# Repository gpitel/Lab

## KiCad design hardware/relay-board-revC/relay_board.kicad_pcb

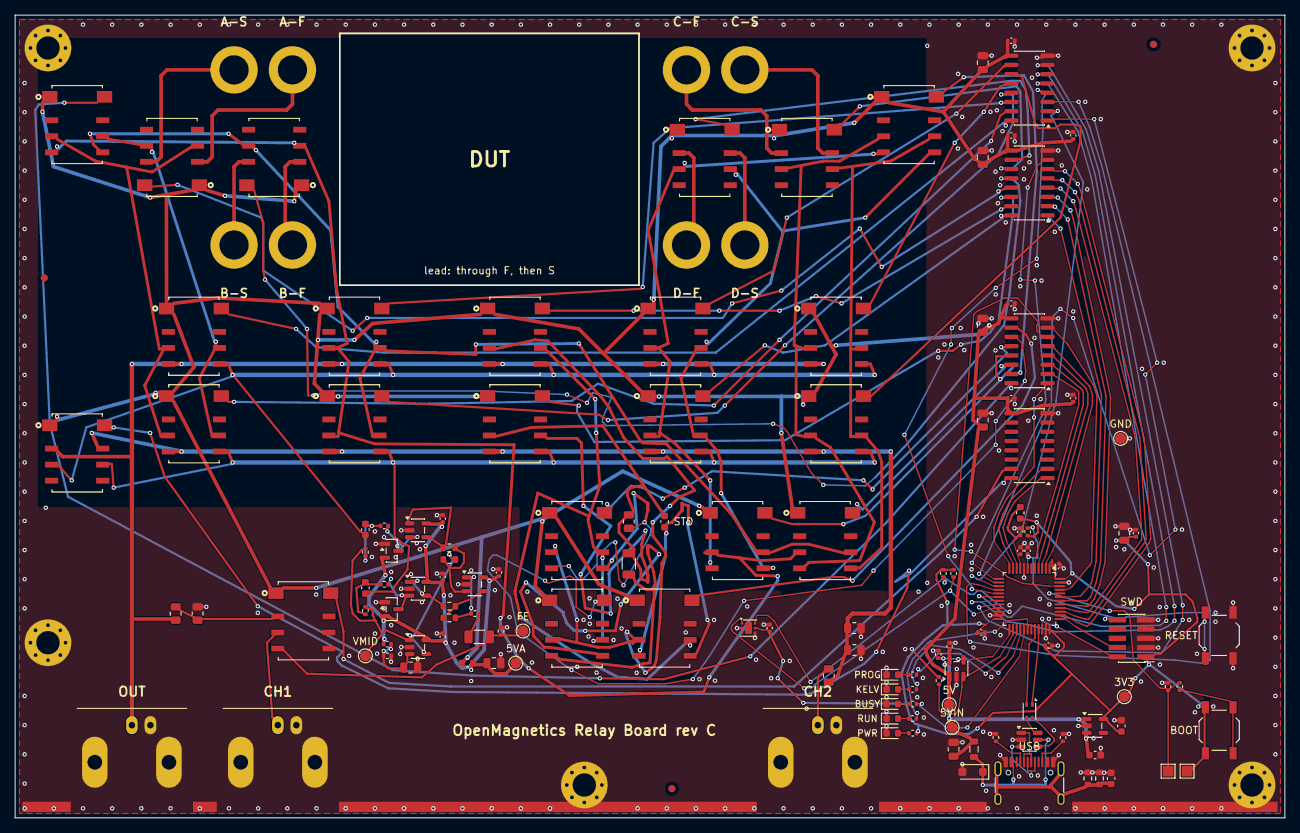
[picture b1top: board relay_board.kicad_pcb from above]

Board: 4 copper layers, 174.0 x 110.0 mm, 158 parts (0 on the bottom side), 126 nets.

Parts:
BOND1, BOND2, BOND3, BOND4, BOND5: GND bonding strip; GND_BondingStrip
C1, C2, C23, C29, C32, C33, C34, C35: C_0805_2012Metric
C3, C4, C20, C21, C30, C31: C_0603_1608Metric
C5, C6, C7, C8, C9, C10, C11, C12, C15, C16, C17, C18, C19, C25, C26, C27, C28, C36, C37: C_0402_1005Metric
C22: C_1206_3216Metric
D1, D5, D6, D7, D8: LED_0603_1608Metric
D2: SOT-23-6
D3, D4: SOT-23
D9: D_SOD-123F
FB1: L_0805_2012Metric
FB2, FB3: L_0603_1608Metric
FID1, FID2, FID3: Fiducial_1mm_Mask2mm
H1, H2, H3, H4, H5: MountingHole_3.2mm_M3_Pad_Via
J1: USB_C_Receptacle_HRO_TYPE-C-31-M-12
J6, J7, J9: BNC_Amphenol_B6252HB-NPP3G-50_Horizontal
J8: PinHeader_2x05_P1.27mm_Vertical_SMD
J10, J11, J12, J13, J14, J15, J16, J17: Grayhill 02-21; Grayhill_02-21_BananaPlug_4mm
K1, K2, K3, K4, K5, K6, K7, K8, K9, K10, K11, K12, K13, K14, K15, K16, K17, K18, K19, K20, K21, K22, K23: G6K-2F-RF-S; Relay_Omron_G6K-2F-RF-S
L1: L_CommonModeChoke_Coilank_ACM2012
NT1, NT2, NT4, NT5: NetTie-2_SMD_Pad0.5mm
R1, R2, R3, R4, R10, R17, R20, R21, R22, R23, R28, R29, R30, R31, R32, R33, R34, R35, R38, R39, R40, R41: R_0402_1005Metric
R5, R12, R13, R14, R15, R16: R_0805_2012Metric
R18: R_1206_3216Metric
R24, R25, R26, R27, R36, R37: R_0603_1608Metric
SW1, SW2: SW_SPST_TL3342
TP1, TP2: TestPoint_Pad_1.5x1.5mm
TP3, TP4, TP5, TP6, TP7, TP8, TP9: TestPoint_Pad_D1.5mm
U1: LQFP-48_7x7mm_P0.5mm
U2, U3, U4, U6: SOIC-16_3.9x9.9mm_P1.27mm
U5, U7, U8, U9, U10, U11: SOT-23-5
U12: WSON-6-1EP_2x2mm_P0.65mm_EP1x1.6mm

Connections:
/+3V3: C2.1, C4.1, C8.1, C9.1, C16.1, C17.1, C36.1, FB3.1, J8.1, R3.1, R32.1, R38.2, R39.2, R41.2, SW1.1, TP2.1, TP5.1, U1.1, U1.24, U1.36, U1.48, U5.5, U12.5
/+3V3A: C18.1, C19.1, FB3.2, U1.9
/+5V: C5.1, C6.1, C7.1, C10.1, C11.1, C12.1, C32.1, C33.1, C34.1, C35.1, FB2.1, K1.1, K2.1, K3.1, K4.1, K5.1, K6.1, K7.1, K8.1, K9.1, K10.1, K11.1, K12.1, K13.1, K14.1, K15.1, K16.1, K17.1, K18.1, K19.1, K20.1, K21.1, K22.1, K23.1, TP3.1, U2.9, U3.9, U4.9, U6.9, U11.1
/+5VA: C25.1, C26.1, C27.1, C28.1, C29.1, D3.2, D4.2, FB2.2, R30.1, TP6.1, U7.5, U8.5, U9.5, U10.5
/+5V_IN: C1.1, C3.1, C37.1, FB1.2, TP4.1, U5.1, U5.3, U11.5
/BOOT0: R4.1, R17.2, TP1.1, U1.44
/BOOT_SW: R17.1, SW1.2
/BUSY_A: D6.2, R33.2
/CAL_E: K9.3, K19.3, K20.3, K21.3
/CAL_ES: K9.6, K19.6, K20.6, K21.6
/CAL_F: C30.2, K10.3, NT2.1, R5.2, R18.2
/CAL_FS: K10.6, NT2.2
/CC1: J1.A5, R1.1
/CC2: J1.B5, R2.1
/CH1_BNC: J7.1, K23.3
/CH1_NODE: K23.2, R12.2, R13.1
/CH2_NODE: J9.1, R16.2
/COIL_EN: R40.1, U1.25, U11.4
/COIL_FLT: R41.1, U1.26, U11.3
/DUTS_A: J11.1, K11.7
/DUTS_B: J13.1, K12.7
/DUTS_C: J15.1, K13.7
/DUTS_D: J17.1, K14.7
/DUT_A: J10.1, K11.2
/DUT_B: J12.1, K12.2
/DUT_C: J14.1, K13.2
/DUT_D: J16.1, K14.2
/FE_AMP: R25.2, R28.1, U9.1
/FE_BN: R24.1, U8.1, U8.4
/FE_BP: R26.1, U7.1, U7.4
/FE_DM: R24.2, R25.1, U9.4
/FE_DP: R26.2, R27.1, U9.3
/FE_INN: C21.2, R22.1, R23.1
/FE_INP: C20.2, R20.1, R21.1
/FE_N: D4.3, R23.2, U8.3
/FE_OUT: C22.2, K23.4, R29.1, TP8.1
/FE_P: D3.3, R21.2, U7.3
/FE_R: C22.1, R28.2
/GND: BOND1.1, BOND2.1, BOND3.1, BOND4.1, BOND5.1, C1.2, C2.2, C3.2, C4.2, C5.2, C6.2, C7.2, C8.2, C9.2, C10.2, C11.2, C12.2, C15.2, C16.2, C17.2, C18.2, C19.2, C23.2, C25.2, C26.2, C27.2, C28.2, C29.2, C31.2, C32.2, C33.2, C34.2, C35.2, C36.2, C37.2, D1.1, D2.2, D3.1, D4.1, D5.1, D6.1, D7.1, D8.1, D9.2, H1.1, H2.1, H3.1, H4.1, H5.1, J1.A1, J1.A12, J1.B1, J1.B12, J6.2, J7.2, J8.3, J8.5, J8.9, J9.2, R1.2, R2.2, R4.2, R13.2, R14.2, R15.2, R29.2, R31.2, R36.2, R37.2, R40.2, SW2.2, TP9.1, U1.8, U1.23, U1.35, U1.47, U2.8, U3.8, U4.8, U5.2, U6.8, U7.2, U8.2, U9.2, U10.2, U11.2, U12.2, U12.4
/GPIO1: U1.14, U2.1
/GPIO2: U1.15, U2.2
/GPIO3: U1.16, U2.3
/GPIO4: U1.17, U2.4
/GPIO5: U1.18, U2.5
/GPIO6: U1.19, U2.6
/GPIO7: U1.20, U2.7
/GPIO8: U1.43, U3.1
/GPIO9: U1.42, U3.2
/GPIO10: U1.41, U3.3
/GPIO11: U1.40, U3.4
/GPIO12: U1.39, U3.5
/GPIO13: U1.38, U3.6
/GPIO14: U1.13, U3.7
/GPIO15: U1.12, U4.1
/GPIO16: U1.5, U4.2
/GPIO17: U1.4, U4.3
/GPIO18: U1.3, U4.4
/GPIO19: U1.2, U4.5
/GPIO20: U1.46, U4.6
/GPIO21: U1.45, U4.7
/GPIO22: U1.10, U6.1
/GPIO23: U1.11, U6.2
/I2C_SCL: R38.1, U1.21, U12.1
/I2C_SDA: R39.1, U1.22, U12.6
/K1_COIL: K1.8, U2.16
/K2_COIL: K2.8, U2.15
/K3_COIL: K3.8, U2.14
/K4_COIL: K4.8, U2.13
/K5_COIL: K5.8, U2.12
/K6_COIL: K6.8, U2.11
/K7_COIL: K7.8, U2.10
/K8_COIL: K8.8, U3.16
/K9_COIL: K9.8, U3.15
/K10_COIL: K10.8, U3.14
/K11_COIL: K11.8, U3.13
/K12_COIL: K12.8, U3.12
/K13_COIL: K13.8, U3.11
/K14_COIL: K14.8, U3.10
/K15_COIL: K15.8, U4.16
/K16_COIL: K16.8, U4.15
/K17_COIL: K17.8, U4.14
/K18_COIL: K18.8, U4.13
/K19_COIL: K19.8, U4.12
/K20_COIL: K20.8, U4.11
/K21_COIL: K21.8, U4.10
/K22_COIL: K22.8, U6.16
/K23_COIL: K23.8, U6.15
/KELVIN_A: D7.2, R34.2
/LED_BUSY: R33.1, U1.29
/LED_KELVIN: R34.1, U1.28
/LED_PROG: R35.1, U1.27
/LED_RUN: R10.1, U1.30
/NRST: C15.1, J8.10, R3.2, SW2.1, U1.7
/PROG_A: D8.2, R35.2
/PWR_A: D5.2, R32.2
/RAIL_HI: J6.1, K1.4, K3.4, K5.4, K7.4, K9.4, K22.2, R12.1
/RAIL_LO: K2.4, K4.4, K6.4, K8.4, K10.4, K22.7, R14.1, R15.1, R16.1
/RUN_A: D1.2, R10.2
/SA: K1.6, K2.6, K11.6, K15.6
/SB: K3.6, K4.6, K12.6, K15.5, K17.6, K18.6
/SC: K5.6, K6.6, K13.6, K16.6, K17.5
/SD: K7.6, K8.6, K14.6, K16.5, K18.5
/SNS_HI: C20.1, K1.5, K3.5, K5.5, K7.5, K9.5, K22.3
/SNS_LO: C21.1, K2.5, K4.5, K6.5, K8.5, K10.5, K22.6
/STD1_F: K19.4, NT1.1, R5.1
/STD1_S: K19.5, NT1.2
/STD2_F: K20.4, NT4.1, R18.1
/STD2_S: K20.5, NT4.2
/STD3_F: C30.1, K21.4, NT5.1
/STD3_S: K21.5, NT5.2
/SWCLK: J8.4, U1.37
/SWDIO: J8.2, U1.34
/TA: K1.3, K2.3, K11.3, K15.3
/TB: K3.3, K4.3, K12.3, K15.4, K17.3, K18.3
/TC: K5.3, K6.3, K13.3, K16.3, K17.4
/TD: K7.3, K8.3, K14.3, K16.4, K18.4
/USB_DM: L1.2, U1.32
/USB_DM_CON: D2.1, J1.A7, J1.B7
/USB_DM_ESD: D2.6, L1.3
/USB_DP: L1.1, U1.33
/USB_DP_CON: D2.3, J1.A6, J1.B6
/USB_DP_ESD: D2.4, L1.4
/USB_SHIELD: C31.1, J1.SH, R36.1, R37.1
/VBUS: D2.5, D9.1, FB1.1, J1.A4, J1.A9, J1.B4, J1.B9
/VMID: R20.2, R22.2, R27.2, TP7.1, U10.1, U10.4
/VMID_DIV: C23.1, R30.2, R31.1, U10.3

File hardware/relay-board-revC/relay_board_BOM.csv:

Comment,Designator,Footprint,Quantity,Manufacturer Part,Description
10uF,"C1,C23,C32,C33,C34,C35",C_0805_2012Metric,6,,C_0805_2012Metric
1uF,C18,C_0402_1005Metric,1,,C_0402_1005Metric
10nF,C19,C_0402_1005Metric,1,,C_0402_1005Metric
4.7uF,"C2,C29",C_0805_2012Metric,2,,C_0805_2012Metric
47uF,C22,C_1206_3216Metric,1,X5R 10 V 1206,front-end output DC block
1uF,"C3,C4,C20,C21",C_0603_1608Metric,4,,C_0603_1608Metric
10pF C0G,C30,C_0603_1608Metric,1,,C_0603_1608Metric
4.7nF 100V,C31,C_0603_1608Metric,1,,C_0603_1608Metric
100nF,"C5,C6,C7,C8,C9,C10,C11,C12,C15,C16,C17,C25,C26,C27,C28,C36,C37",C_0402_1005Metric,17,,C_0402_1005Metric
RUN,D1,LED_0603_1608Metric,1,0603 LED green,status: firmware running / USB host
USBLC6-2SC6,D2,SOT-23-6,1,ST USBLC6-2SC6,"USB 2.0 ESD array, IEC 61000-4-2 level 4"
BAV99,"D3,D4",SOT-23,2,"Nexperia BAV99,215",front-end input clamp
PWR,D5,LED_0603_1608Metric,1,0603 LED green,status: power
BUSY,D6,LED_0603_1608Metric,1,0603 LED amber,status: relays switching
KELVIN,D7,LED_0603_1608Metric,1,0603 LED blue,status: Kelvin mode
PROG,D8,LED_0603_1608Metric,1,0603 LED red (KT-0603R),status: DFU / firmware update
SMF5.0A,D9,D_SOD-123F,1,,D_SOD-123F
220R@100MHz 2A,FB1,L_0805_2012Metric,1,Murata BLM21PG221SN1D,"VBUS ferrite, 2 A"
600R@100MHz,"FB2,FB3",L_0603_1608Metric,2,Sunlord GZ1608D601TF,"ferrite, 200 mA (VDDA, +5VA)"
USB-C,J1,USB_C_Receptacle_HRO_TYPE-C-31-M-12,1,HRO TYPE-C-31-M-12,"USB-C receptacle, USB 2.0, 16 pin"
DUT A F,J10,Grayhill_02-21_BananaPlug_4mm,1,Grayhill 02-21 miniature test clip (banana plug),"Kelvin pair per terminal (F/S, 8 mm apart); plug straight into the plated 4.0 mm hole, hand-fitted (solder for a permanent fixture)"
DUT A S,J11,Grayhill_02-21_BananaPlug_4mm,1,Grayhill 02-21 miniature test clip (banana plug),"Kelvin pair per terminal (F/S, 8 mm apart); plug straight into the plated 4.0 mm hole, hand-fitted (solder for a permanent fixture)"
DUT B F,J12,Grayhill_02-21_BananaPlug_4mm,1,Grayhill 02-21 miniature test clip (banana plug),"Kelvin pair per terminal (F/S, 8 mm apart); plug straight into the plated 4.0 mm hole, hand-fitted (solder for a permanent fixture)"
DUT B S,J13,Grayhill_02-21_BananaPlug_4mm,1,Grayhill 02-21 miniature test clip (banana plug),"Kelvin pair per terminal (F/S, 8 mm apart); plug straight into the plated 4.0 mm hole, hand-fitted (solder for a permanent fixture)"
DUT C F,J14,Grayhill_02-21_BananaPlug_4mm,1,Grayhill 02-21 miniature test clip (banana plug),"Kelvin pair per terminal (F/S, 8 mm apart); plug straight into the plated 4.0 mm hole, hand-fitted (solder for a permanent fixture)"
DUT C S,J15,Grayhill_02-21_BananaPlug_4mm,1,Grayhill 02-21 miniature test clip (banana plug),"Kelvin pair per terminal (F/S, 8 mm apart); plug straight into the plated 4.0 mm hole, hand-fitted (solder for a permanent fixture)"
DUT D F,J16,Grayhill_02-21_BananaPlug_4mm,1,Grayhill 02-21 miniature test clip (banana plug),"Kelvin pair per terminal (F/S, 8 mm apart); plug straight into the plated 4.0 mm hole, hand-fitted (solder for a permanent fixture)"
DUT D S,J17,Grayhill_02-21_BananaPlug_4mm,1,Grayhill 02-21 miniature test clip (banana plug),"Kelvin pair per terminal (F/S, 8 mm apart); plug straight into the plated 4.0 mm hole, hand-fitted (solder for a permanent fixture)"
BNC SOURCE,J6,BNC_Amphenol_B6252HB-NPP3G-50_Horizontal,1,Amphenol B6252HB-NPP3G-50,50R right-angle BNC jack
BNC CH1,J7,BNC_Amphenol_B6252HB-NPP3G-50_Horizontal,1,Amphenol B6252HB-NPP3G-50,50R right-angle BNC jack
SWD,J8,PinHeader_2x05_P1.27mm_Vertical_SMD,1,CNC Tech 3220-10-0300-00,"1.27 mm 2x5 Cortex debug header, SMD"
BNC CH2,J9,BNC_Amphenol_B6252HB-NPP3G-50_Horizontal,1,Amphenol B6252HB-NPP3G-50,50R right-angle BNC jack
G6K-2F-RF-S DC5,"K1,K2,K3,K4,K5,K6,K7,K8,K9,K10,K11,K12,K13,K14,K15,K16,K17,K18,K19,K20,K21,K22,K23",Relay_Omron_G6K-2F-RF-S,23,Omron G6K-2F-RF-S DC5,"high-frequency DPDT relay, 5 V coil"
90R CM,L1,L_CommonModeChoke_Coilank_ACM2012,1,TDK ACM2012-900-2P-T002,"USB CM choke, 90R @100 MHz; windings 1-4 / 2-3"
5.1k,"R1,R2",R_0402_1005Metric,2,,R_0402_1005Metric
4.7k,"R10,R32,R33,R35,R38,R39",R_0402_1005Metric,6,,R_0402_1005Metric
1k 0.1%,R12,R_0805_2012Metric,1,Vishay TNPW08051K00BEEA,bridge RV1: 1k 0.1% 25 ppm thin film
47R 0.1%,"R13,R16",R_0805_2012Metric,2,Vishay TNPW080547R0BEEA,bridge RV2/RC2: 47R 0.1% 25 ppm thin film
4R7,"R14,R15",R_0805_2012Metric,2,UNI-ROYAL TC0525B470KT5G (LCSC C21571495),"bridge RC1 shunt half: 4R7 0.1% 25 ppm thin film, JLC stock (two in parallel = 2R35); equivalent: Vishay TNPW08054R70BEEA"
1k,"R17,R34",R_0402_1005Metric,2,,R_0402_1005Metric
1R 0.5%,R18,R_1206_3216Metric,1,,R_1206_3216Metric
100k,"R20,R22,R29,R40",R_0402_1005Metric,4,,R_0402_1005Metric
100R,"R21,R23",R_0402_1005Metric,2,,R_0402_1005Metric
1k 0.1%,"R24,R25,R26,R27",R_0603_1608Metric,4,Yageo RT0603BRD071KL,"front-end difference stage, 0.1 % 25 ppm"
49.9R,R28,R_0402_1005Metric,1,,R_0402_1005Metric
10k,"R3,R4,R31,R41",R_0402_1005Metric,4,,R_0402_1005Metric
18k,R30,R_0402_1005Metric,1,,R_0402_1005Metric
1M,R36,R_0603_1608Metric,1,,R_0603_1608Metric
0R,R37,R_0603_1608Metric,1,,R_0603_1608Metric
100R 0.1%,R5,R_0805_2012Metric,1,Vishay TNPW0805100RBEEA,LOAD standard: 100R 0.1% 25 ppm thin film
BOOT,SW1,SW_SPST_TL3342,1,C&K TL3342F160QG (or XKB TS-1187A-B-A-B),SMD tact switch: hold at power-up for ROM DFU
RESET,SW2,SW_SPST_TL3342,1,C&K TL3342F160QG (or XKB TS-1187A-B-A-B),SMD tact switch: NRST
STM32F072CBT6,U1,LQFP-48_7x7mm_P0.5mm,1,ST STM32F072CBT6,"Cortex-M0, 128K flash, crystal-less USB (HSI48 + CRS)"
TPS2051CDBV,U11,SOT-23-5,1,,SOT-23-5
TMP117AIDRV,U12,WSON-6-1EP_2x2mm_P0.65mm_EP1x1.6mm,1,,WSON-6-1EP_2x2mm_P0.65mm_EP1x1.6mm
TBD62003APG,"U2,U3,U4,U6",SOIC-16_3.9x9.9mm_P1.27mm,4,Toshiba TBD62003AFG,7ch DMOS sink driver (SOIC-16 = AFG suffix)
AP2112K-3.3,U5,SOT-23-5,1,Diodes AP2112K-3.3TRG1,"3.3 V 600 mA LDO, 250 mV dropout"
OPA356,"U7,U8,U9,U10",SOT-23-5,4,TI OPA356AIDBVR,"200 MHz RRO op-amp, single 2.5-5.5 V (Kelvin front-end)"

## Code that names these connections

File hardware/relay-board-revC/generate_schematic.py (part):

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            "A5": "CC1", "B5": "CC2",
            "A6": "USB_DP_CON", "B6": "USB_DP_CON",
            "A7": "USB_DM_CON", "B7": "USB_DM_CON",
            "S1": "USB_SHIELD",     # shield: KiCad 9 symbol pin name
            "SH": "USB_SHIELD",     # shield: KiCad 10 symbol pin name
        }
        for pin, net_name in usb.items():
            try:
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        self.net("U1", MCU["BOOT0"], "BOOT0")
        self.net("U1", MCU["PA13"], "SWDIO")
        self.net("U1", MCU["PA14"], "SWCLK")
        self.net("U1", MCU["PA11"], "USB_DM")
        self.net("U1", MCU["PA12"], "USB_DP")
        # RUN on the south row too (PA9): every LED line leaves the MCU
        # westward with the coil-switch lines to the LED column south-west of
        # it; on PC13 (north row) it would cut across the relay lanes
        self.net("U1", MCU["PA9"], "LED_RUN")
        # south row, west to east: coil switch (U11 is south-west), then LEDs
        # (PROG off PA9/PA10/PA14/PA15: the ROM bootloader drives those)
        self.net("U1", MCU["PB12"], "COIL_EN")
        self.net("U1", MCU["PB13"], "COIL_FLT")
        self.net("U1", MCU["PB14"], "LED_PROG")
        self.net("U1", MCU["PB15"], "LED_KELVIN")
        self.net("U1", MCU["PA8"], "LED_BUSY")
        self.net("U1", MCU["PB10"], "I2C_SCL")         # I2C2 (AF1), west pins
        self.net("U1", MCU["PB11"], "I2C_SDA")

        # TMP117 (+/-0.1 C) beside the standards column: every calibration
        # and sweep records the fixture temperature (R5 25 ppm/K, contacts).
        self.add("Sensor_Temperature:TMP117xxDRV", "U12", "TMP117AIDRV", 560, 200,
                 "Package_SON:WSON-6-1EP_2x2mm_P0.65mm_EP1x1.6mm",
                 Description="fixture temperature, I2C 0x48")
        for pin, net_name in (("1", "I2C_SCL"), ("6", "I2C_SDA"), ("5", "+3V3"),
                              ("2", "GND"), ("4", "GND")):
            self.net("U12", pin, net_name)
        self.unused("U12", "3")
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
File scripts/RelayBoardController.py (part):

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}
#: K13/K14: the LOAD-standard column -- one 100R 0.1% between two full-length
#: column buses, reached through the same contact structure as a terminal.
LOAD_HI_BIT = 12             # K13: CAL_E -> RAIL_HI
LOAD_LO_BIT = 13             # K14: CAL_F -> RAIL_LO
#: K15..K18: per-terminal isolation. COM = terminal node, NC = clamp,
#: NO = nothing (the open contact IS the open standard).
ISOLATE_BITS = {"A": 14, "B": 15, "C": 16, "D": 17}
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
